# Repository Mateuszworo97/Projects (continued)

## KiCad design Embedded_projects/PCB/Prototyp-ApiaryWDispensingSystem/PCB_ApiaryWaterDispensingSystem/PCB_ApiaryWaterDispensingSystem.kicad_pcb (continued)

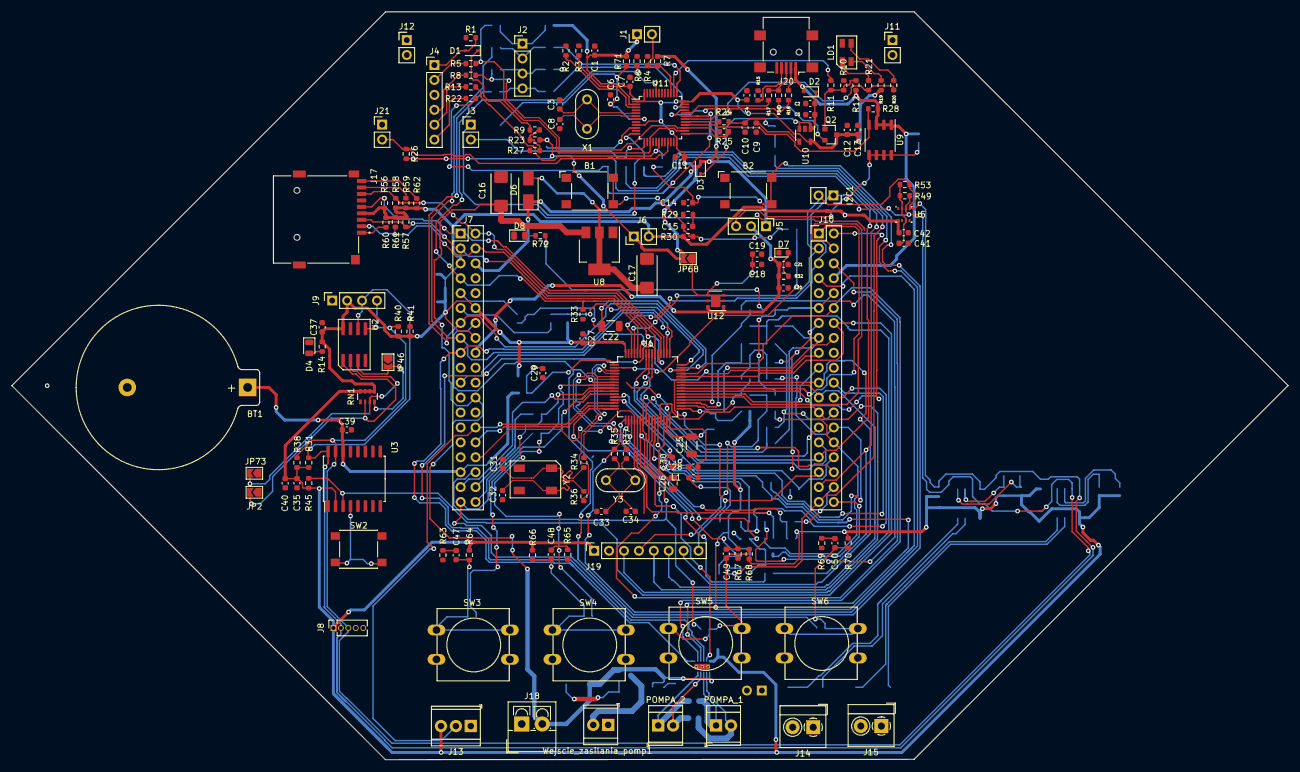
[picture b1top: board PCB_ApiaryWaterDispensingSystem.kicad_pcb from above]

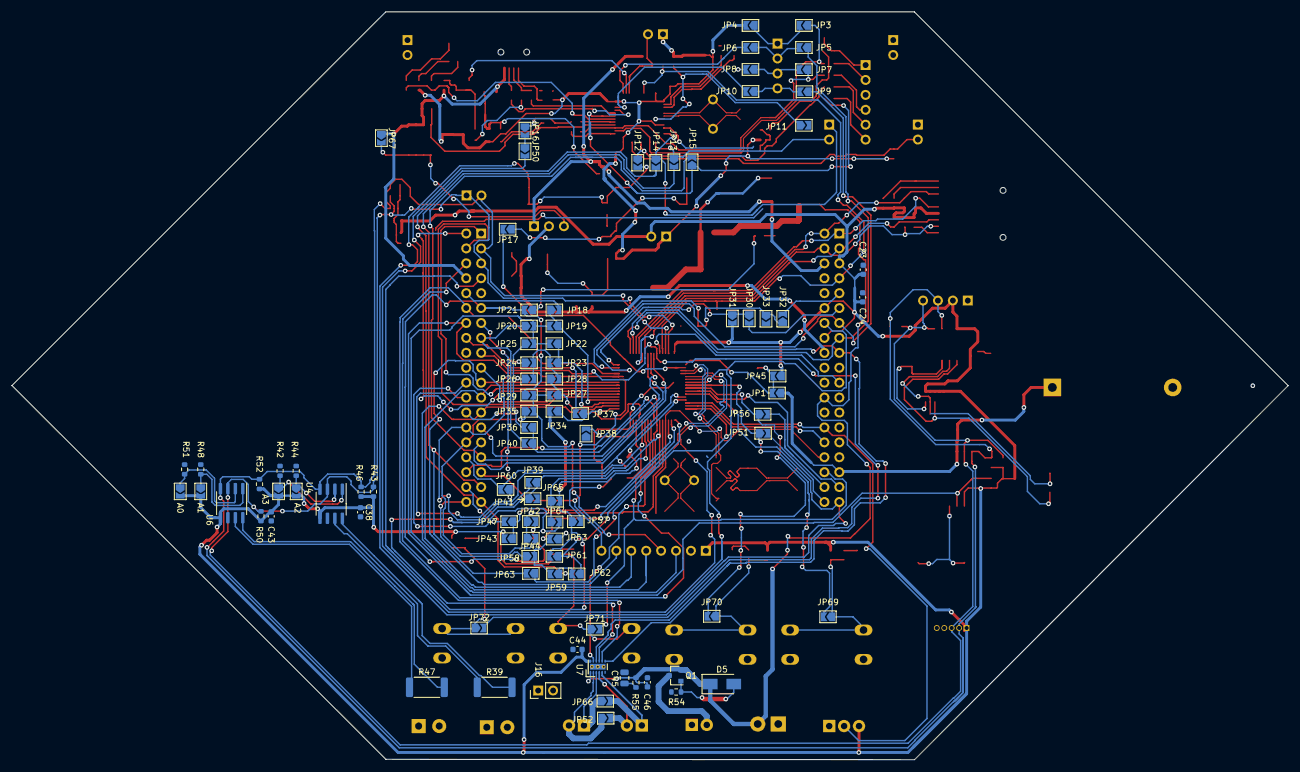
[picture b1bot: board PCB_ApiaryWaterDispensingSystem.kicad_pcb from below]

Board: 2 copper layers, 217.3 x 127.3 mm, 255 parts (94 on the bottom side), 180 nets.

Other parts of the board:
C44, C46: 100n; C_0603_1608Metric
C45: 10u; C_0805_2012Metric
D5: D_Schottky 6,8 V SMAZ6V8; D_SMA
D6: D_Small; D_SMA
D7: LED; D_0603_1608Metric
J16, J21: Conn_02x01; PinHeader_1x02_P2.54mm_Vertical
J18: Conn_01x02; TerminalBlock_4Ucon_1x02_P3.50mm_Vertical
J20: USB_B_Micro; USB_Mini-B_Lumberg_2486_01_Horizontal
JP52, JP66: Jumper_NO_Small; SolderJumper-2_P1.3mm_Open_TrianglePad1.0x1.5mm
JP67, JP68: Jumper_2_Open; SolderJumper-2_P1.3mm_Open_TrianglePad1.0x1.5mm
LD1: LD_BICOLOR_CMS; LD_BiCOLOR_CMS
Q1: Q_PMOS_GSD; SOT-23
Q2: Q_NPN_BEC; SOT-23
R54, R71: 100k; R_0603_1608Metric
R55: 1; R_0603_1608Metric
U7: drv8835; WSON-12-1EP_3x2mm_P0.5mm_EP1x2.65_ThermalVias
U8: LD1117S50TR_SOT223; SOT-223-3_TabPin2
U9: STS7PF30L; SO-8_3.9x4.9mm_P1.27mm
U10: LD3985M33R_SOT23; SOT-23-5
U11: STM32F103CBTx; LQFP-48_7x7mm_P0.5mm
U12: LD39050PU33; WSON-6-1EP_3x3mm_P0.95mm
Wejscie_zasilania_pomp1: Conn_01x02; TerminalBlock_TE_282834-2_1x02_P2.54mm_Horizontal

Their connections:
+5V: U12.1, U12.6; also elsewhere on the board
+5VA: D6.1; also elsewhere on the board
+5VP: J20.1, JP67.1, U9.1, U9.2, U9.3; also elsewhere on the board
/Microcontroller_F1/OSC+: U11.5; also elsewhere on the board
/Microcontroller_F1/OSC-: U11.6; also elsewhere on the board
AENABLE: U7.9; also elsewhere on the board
AIN_1: U11.10; also elsewhere on the board
APHASE: U7.10; also elsewhere on the board
BENABLE: U7.7; also elsewhere on the board
BOOT0: U11.44; also elsewhere on the board
BPHASE: U7.8; also elsewhere on the board
GNDA: C45.2, C46.2, J16.2, R54.2, Wejscie_zasilania_pomp1.1
LED_STLINK: U11.30; also elsewhere on the board
MODE: U7.11; also elsewhere on the board
unnamed 48: U10.1, U10.3; also elsewhere on the board
unnamed 49: U10.4; also elsewhere on the board
unnamed 52: D6.2, U8.2; also elsewhere on the board
unnamed 53: JP68.1, U12.4; also elsewhere on the board
unnamed: C45.1, R55.2
unnamed: D5.2, Q1.1, R54.1
unnamed 70: D7.2; also elsewhere on the board
unnamed 79: JP67.2, U9.5, U9.6, U9.7, U9.8; also elsewhere on the board
unnamed 86: J20.2; also elsewhere on the board
unnamed 87: J20.3; also elsewhere on the board
unnamed 88: J20.4; also elsewhere on the board
unnamed 105: LD1.2; also elsewhere on the board
unnamed 106: LD1.3; also elsewhere on the board
unnamed 107: LD1.4; also elsewhere on the board
unnamed 108: Q2.1; also elsewhere on the board
unnamed 109: Q2.2; also elsewhere on the board
unnamed 110: U11.3; also elsewhere on the board
unnamed 111: U11.2; also elsewhere on the board
unnamed 112: U11.29; also elsewhere on the board
PWR_ENn: U9.4, U11.28; also elsewhere on the board
PWR_EXT: U11.39; also elsewhere on the board
STM_JTCK: U11.37; also elsewhere on the board
STM_JTMS: U11.34; also elsewhere on the board
STM_RST: R71.1, U11.7; also elsewhere on the board
ST_LINK_RX: U11.13; also elsewhere on the board
ST_LINK_TX: U11.12; also elsewhere on the board
T_JTCK: U11.15, U11.26; also elsewhere on the board
T_JTMS: U11.27; also elsewhere on the board
T_NRST: U11.18; also elsewhere on the board
T_SWDIO_IN: U11.25; also elsewhere on the board
T_SWO: U11.31; also elsewhere on the board
USB_DM: U11.32; also elsewhere on the board
USB_DP: U11.33; also elsewhere on the board
USB_RENUMn: U11.38; also elsewhere on the board
VDD: C44.1, U7.12; also elsewhere on the board
VIN: Q1.3, Wejscie_zasilania_pomp1.2
VM: C46.1, D5.1, J18.2, Q1.2, R55.1, U7.1, U8.3; also elsewhere on the board

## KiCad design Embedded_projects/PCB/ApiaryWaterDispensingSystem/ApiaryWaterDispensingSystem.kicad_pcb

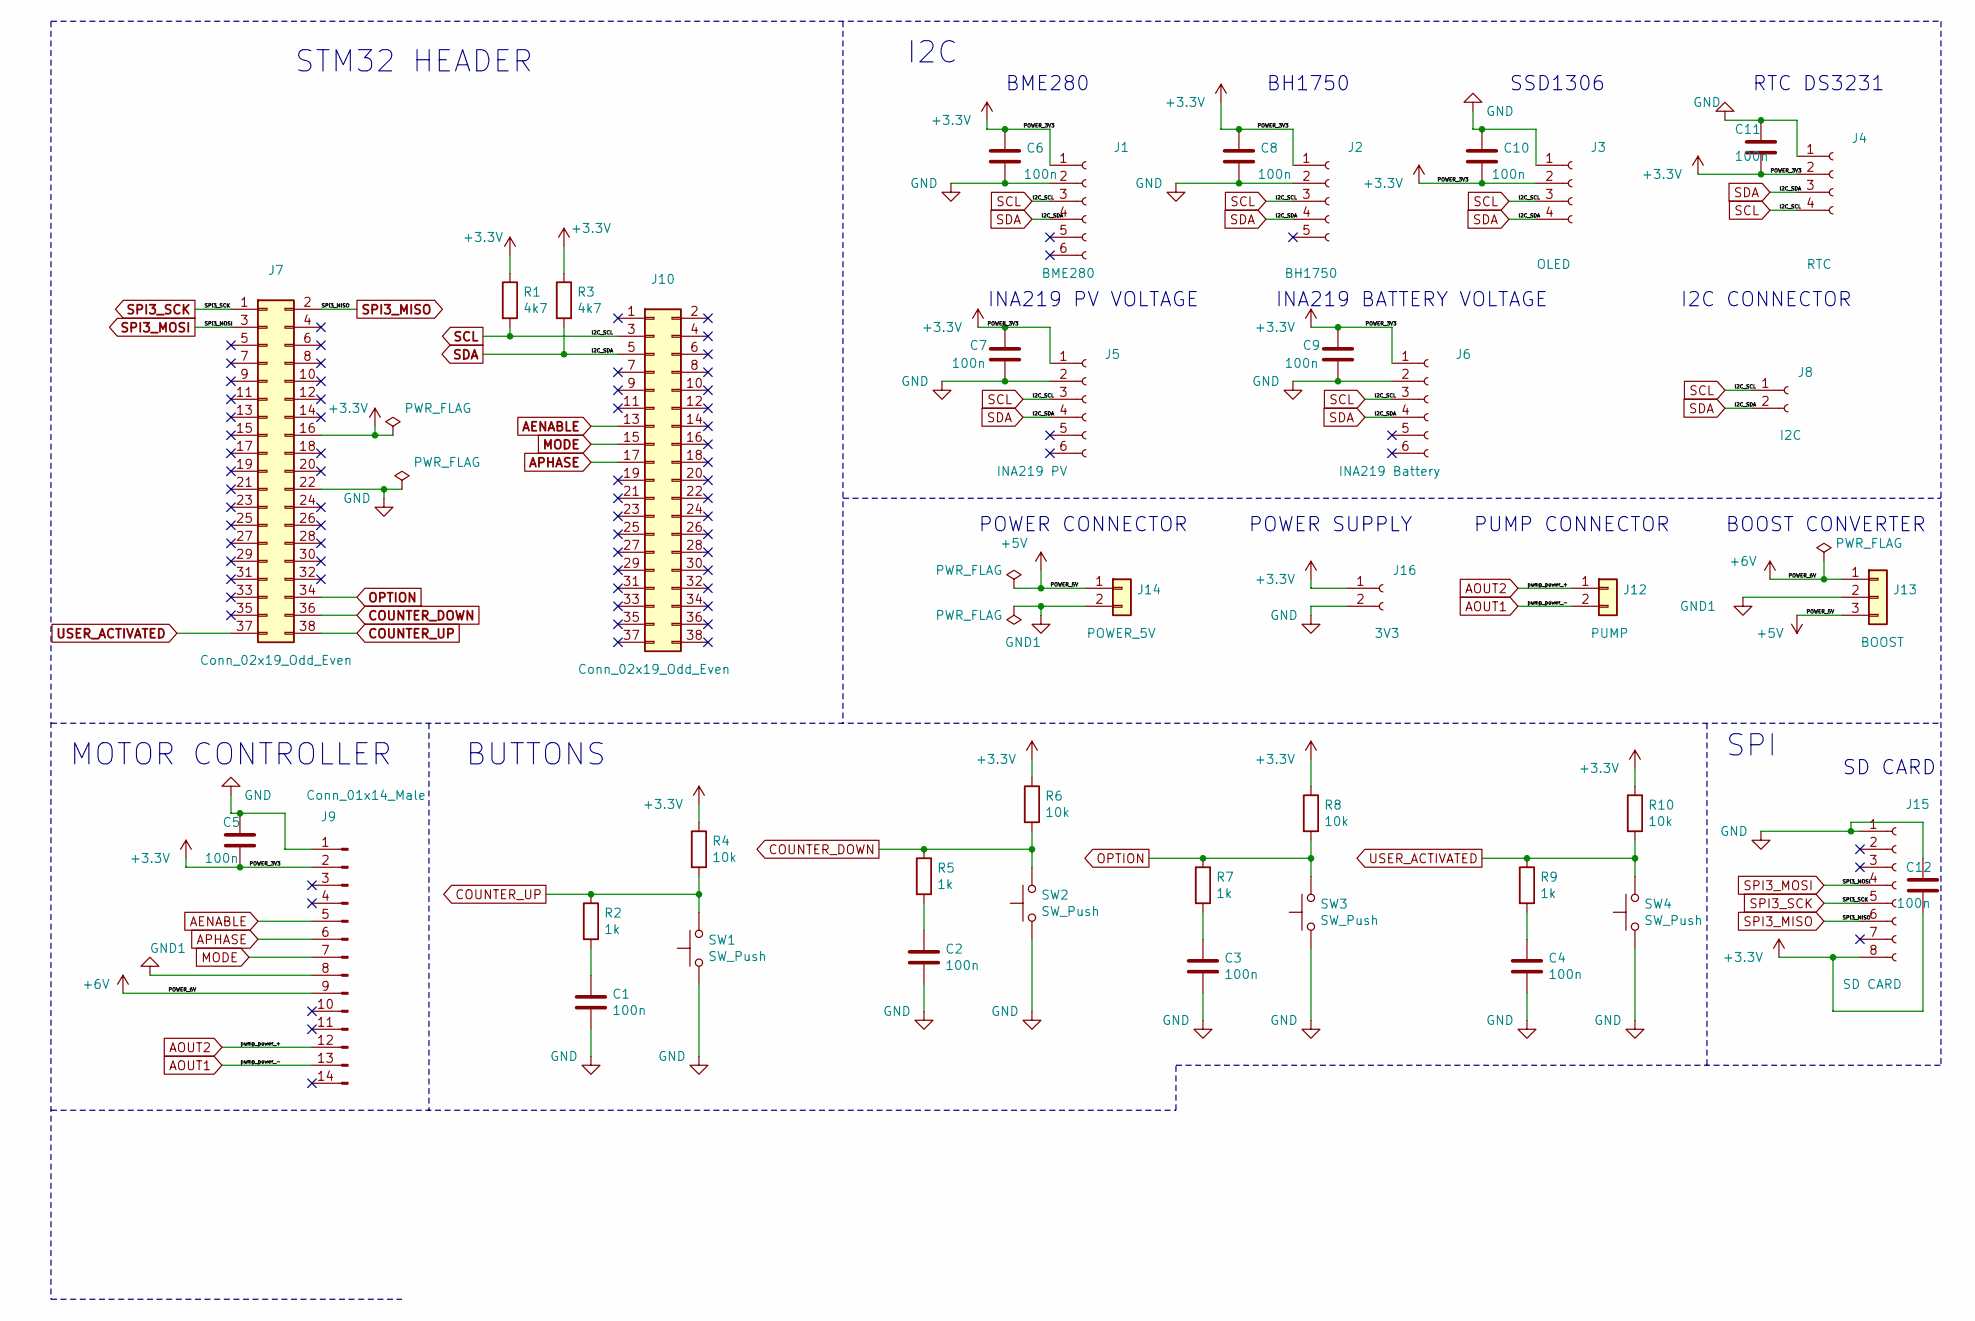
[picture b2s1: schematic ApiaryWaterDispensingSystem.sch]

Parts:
C1, C2, C3, C4, C5, C6, C7, C8, C9, C10, C11, C12: 100n; C_0805_2012Metric
J1: BME280; PinSocket_1x06_P2.54mm_Vertical_BME280
J2: BH1750; PinSocket_1x05_P2.54mm_Vertical
J3: OLED; PinSocket_1x04_P2.54mm_Vertical
J4: RTC; PinSocket_1x04_P2.54mm_Vertical_RTCDS3231
J5: INA219 PV; PinSocket_1x06_P2.54mm_Vertical
J6: INA219 Battery; PinSocket_1x06_P2.54mm_Vertical
J7, J10: Conn_02x19_Odd_Even; PinSocket_2x19_P2.54mm_Vertical
J8: I2C; PinSocket_1x02_P2.54mm_Vertical
J9: Conn_01x14_Male; PinSocket_1x07_P2.54mm_Vertical_DRV8835
J12: PUMP; TerminalBlock_TE_282834-2_1x02_P2.54mm_Horizontal
J13: BOOST; PinSocket_1x03_P2.00mm_Vertical
J14: POWER_5V; TerminalBlock_TE_282834-2_1x02_P2.54mm_Horizontal
J15: SD CARD; PinSocket_1x08_P2.54mm_Vertical_SD_CARD
J16: 3V3; PinSocket_1x02_P2.54mm_Vertical
R1, R3: 4k7; R_0805_2012Metric
R2, R5, R7, R9: 1k; R_0805_2012Metric
R4, R6, R8, R10: 10k; R_0805_2012Metric
SW1, SW2, SW3, SW4: SW_Push; SW_PUSH-12mm

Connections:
+3V3: C5.2, C6.1, C7.1, C8.1, C9.1, C10.2, C11.2, C12.2, J1.1, J2.1, J3.2, J4.2, J5.1, J6.1, J7.16, J9.2, J15.8, J16.1, R1.1, R3.1, R4.1, R6.1, R8.1, R10.1
+5V: J13.3, J14.1
+6V: J9.9, J13.1
AENABLE: J9.5, J10.13
AOUT1: J9.13, J12.2
AOUT2: J9.12, J12.1
APHASE: J9.6, J10.17
COUNTER_DOWN: J7.36, R5.1, R6.2, SW2.2
COUNTER_UP: J7.38, R2.1, R4.2, SW1.2
GND: C1.2, C2.2, C3.2, C4.2, C5.1, C6.2, C7.2, C8.2, C9.2, C10.1, C11.1, C12.1, J1.2, J2.2, J3.1, J4.1, J5.2, J6.2, J7.22, J9.1, J15.1, J16.2, SW1.1, SW2.1, SW3.1, SW4.1
GND1: J9.8, J13.2, J14.2
MODE: J9.7, J10.15
unnamed: C1.1, R2.2
unnamed: C2.1, R5.2
unnamed: C3.1, R7.2
unnamed: C4.1, R9.2
OPTION: J7.34, R7.1, R8.2, SW3.2
SCL: J1.3, J2.3, J3.3, J4.4, J5.3, J6.3, J8.1, J10.3, R1.2
SDA: J1.4, J2.4, J3.4, J4.3, J5.4, J6.4, J8.2, J10.5, R3.2
SPI3_MISO: J7.2, J15.6
SPI3_MOSI: J7.3, J15.4
SPI3_SCK: J7.1, J15.5
USER_ACTIVATED: J7.37, R9.1, R10.2, SW4.2

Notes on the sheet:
STM32 HEADER
I2C
BH1750
SSD1306
INA219 PV VOLTAGE
INA219 BATTERY VOLTAGE
SD CARD
RTC DS3231
BME280
PUMP CONNECTOR
I2C CONNECTOR
BOOST CONVERTER
SPI
POWER SUPPLY
BUTTONS
POWER CONNECTOR
MOTOR CONTROLLER

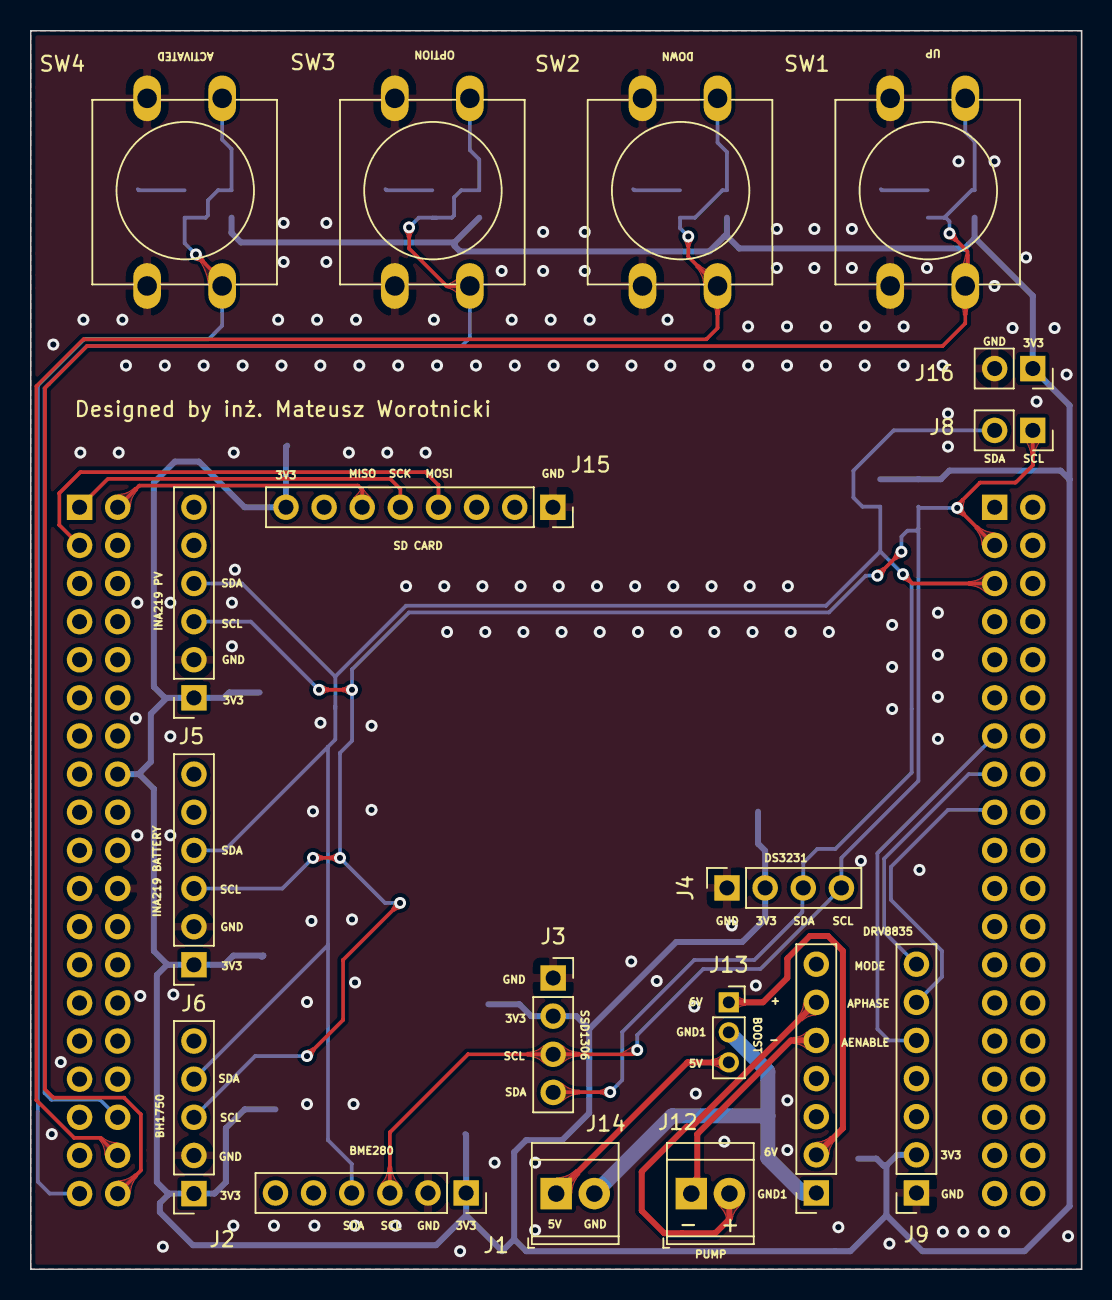
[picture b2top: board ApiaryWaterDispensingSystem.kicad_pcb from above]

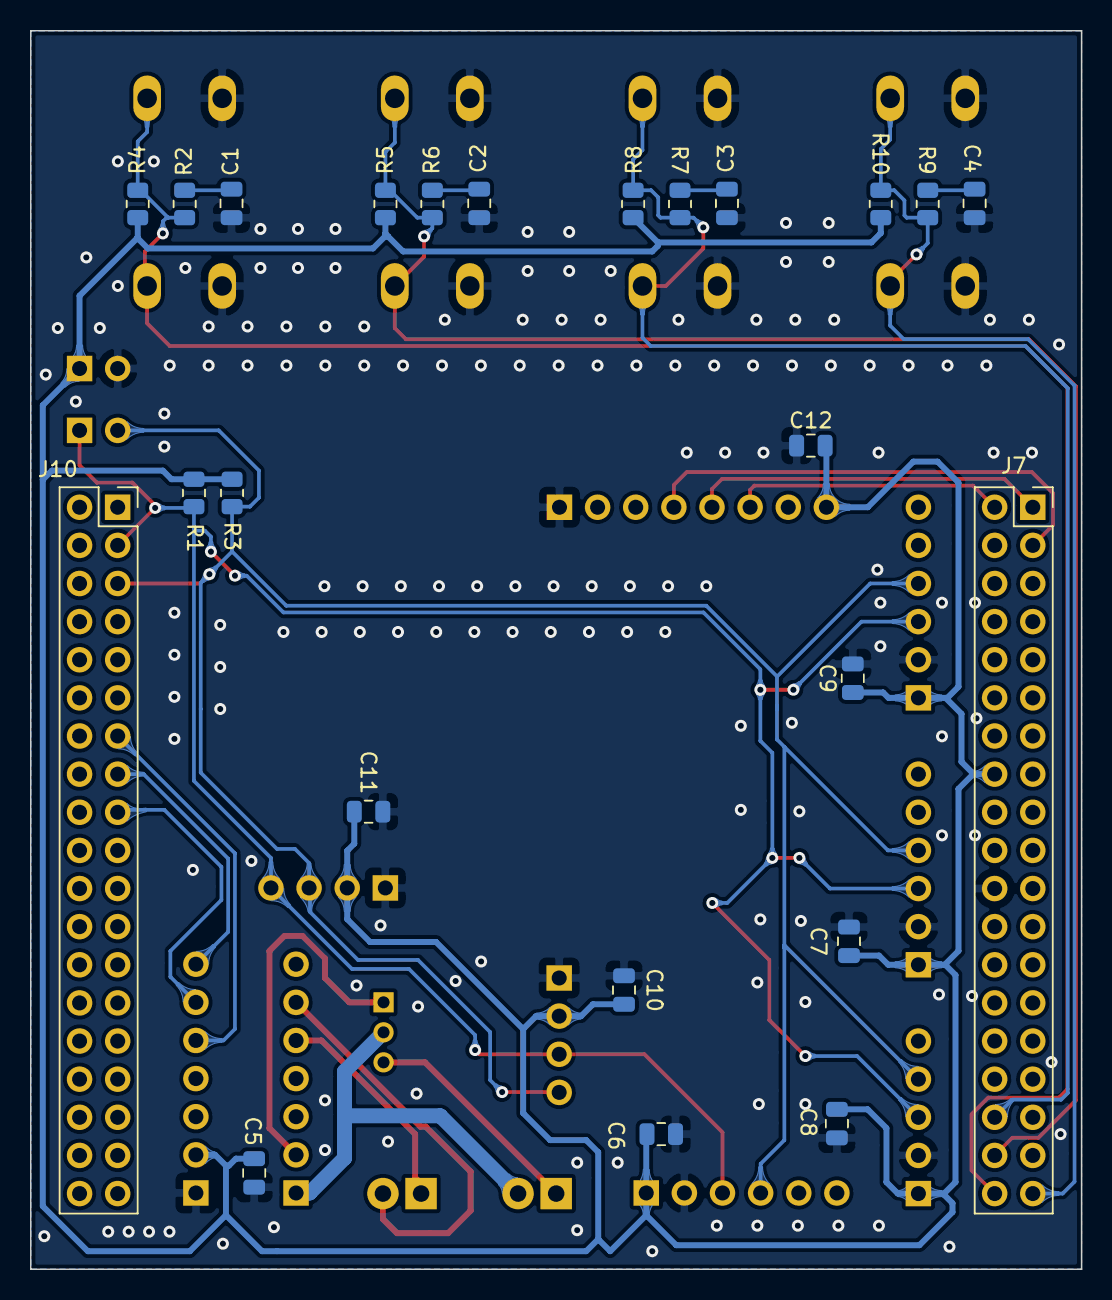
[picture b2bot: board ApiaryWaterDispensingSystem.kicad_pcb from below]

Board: 2 copper layers, 70.0 x 82.5 mm, 41 parts (24 on the bottom side), 23 nets.

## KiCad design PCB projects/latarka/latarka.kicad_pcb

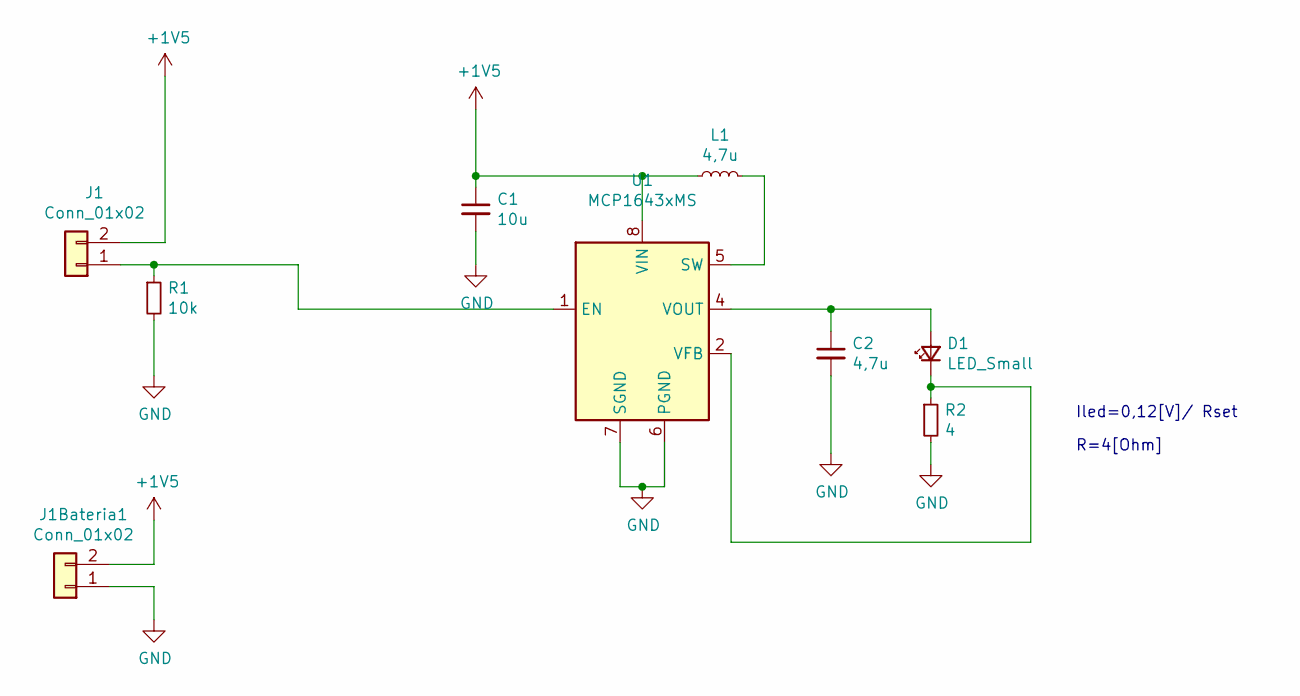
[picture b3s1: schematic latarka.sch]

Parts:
C1: 10u; C_0805_2012Metric_Pad1.18x1.45mm_HandSolder
C2: 4,7u; C_0805_2012Metric_Pad1.18x1.45mm_HandSolder
D1: LED_Small; LED_D8.0mm
J1, J1Bateria1: Conn_01x02; PinHeader_1x02_P2.54mm_Vertical
L1: 4,7u; cewka_m2
R1: 10k; R_0805_2012Metric_Pad1.20x1.40mm_HandSolder
R2: 4; R_0805_2012Metric_Pad1.20x1.40mm_HandSolder
U1: MCP1643xMS; MSOP-8_3x3mm_P0.65mm

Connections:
+1V5: C1.1, J1.2, J1Bateria1.2, L1.1, U1.8 (VIN)
GND: C1.2, C2.2, J1Bateria1.1, R1.2, R2.2, U1.6 (PGND), U1.7 (SGND)
unnamed: C2.1, D1.2 (A), U1.4 (VOUT)
unnamed: D1.1 (K), R2.1, U1.2 (VFB)
unnamed: J1.1, R1.1, U1.1 (EN)
unnamed: L1.2, U1.5 (SW)

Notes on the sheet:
Iled=0,12[V]/ Rset
R=4[Ohm]

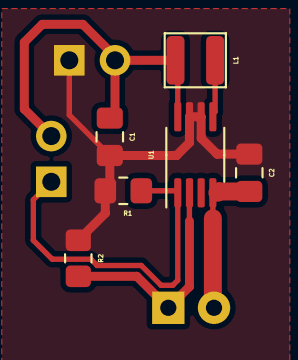
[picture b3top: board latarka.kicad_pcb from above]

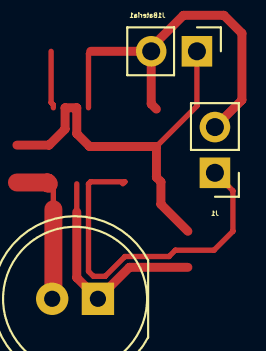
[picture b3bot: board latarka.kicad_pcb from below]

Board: 2 copper layers, 9 parts (3 on the bottom side), 6 nets.

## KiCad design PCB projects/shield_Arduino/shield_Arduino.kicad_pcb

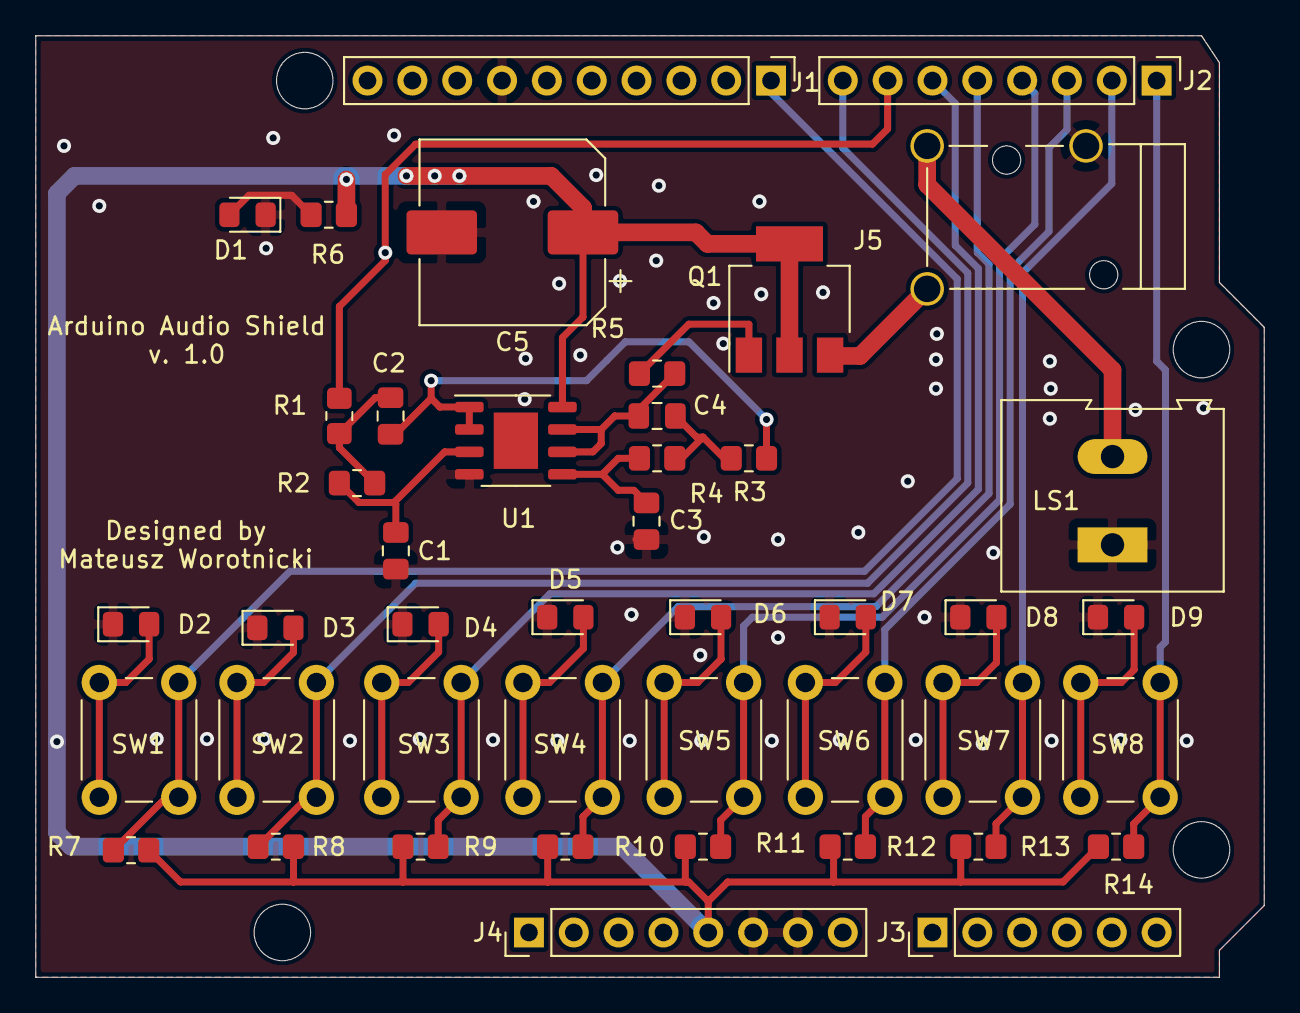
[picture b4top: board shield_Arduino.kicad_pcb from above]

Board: 2 copper layers, 69.6 x 53.3 mm, 45 parts (0 on the bottom side), 29 nets.

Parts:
C1, C3: 1nF; C_0805_2012Metric_Pad1.18x1.45mm_HandSolder
C2: 27n; C_0805_2012Metric_Pad1.18x1.45mm_HandSolder
C4: 56mF; C_0805_2012Metric_Pad1.18x1.45mm_HandSolder
C5: 1000uF; CP_Elec_10x10
D1, D2, D3, D4, D5, D6, D7, D8, D9: LED; LED_0805_2012Metric_Pad1.15x1.40mm_HandSolder
J1: Conn_01x10_Male; PinHeader_1x10_P2.54mm_Vertical
J2, J4: Conn_01x08_Male; PinHeader_1x08_P2.54mm_Vertical
J3: Conn_01x06_Male; PinHeader_1x06_P2.54mm_Vertical
J5: AudioJack2_SwitchT; Jack_3.5mm_Lumberg_150304_Horizontal
LS1: Speaker; TerminalBlock_Altech_AK300-2_P5.00mm
Q1: BCP56; SOT-223-3_TabPin2
R1: 13k; R_0805_2012Metric_Pad1.20x1.40mm_HandSolder
R2: 27k; R_0805_2012Metric_Pad1.20x1.40mm_HandSolder
R3: 1k6; R_0805_2012Metric_Pad1.20x1.40mm_HandSolder
R4: 3k; R_0805_2012Metric_Pad1.20x1.40mm_HandSolder
R5: 120; R_0805_2012Metric_Pad1.20x1.40mm_HandSolder
R6, R7, R8, R9, R10, R11, R12, R13, R14: 220; R_0805_2012Metric_Pad1.20x1.40mm_HandSolder
SW1, SW2, SW3, SW4, SW5, SW6, SW7, SW8: SWITCH; SW_PUSH_6mm_H5mm
U1: MCP6002-xSN; SOIC-8-1EP_3.9x4.9mm_P1.27mm_EP2.514x3.2mm
e: MountingHole_3.2mm_M3

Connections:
+5V: C5.1, J4.5, Q1.2, R6.1, R7.1, R8.1, R9.1, R10.1, R11.1, R12.1, R13.1, R14.1, U1.8
/AUDIO_WAVE: C4.1, R5.2, U1.6, U1.7
AUDIO_PWM: J2.7, R1.2
BTN_1: J2.1, R14.2, SW8.2
BTN_2: J2.2, R13.2, SW7.2
BTN_3: J2.3, R12.2, SW6.2
BTN_4: J2.4, R11.2, SW5.2
BTN_5: J2.5, R10.2, SW4.2
BTN_6: J2.6, R9.2, SW3.2
BTN_7: J2.8, R8.2, SW2.2
BTN_8: J1.1, R7.2, SW1.2
GND: C1.2, C3.2, C5.2, D1.1, D2.1, D3.1, D4.1, D5.1, D6.1, D7.1, D8.1, D9.1, J1.7, J4.6, J4.7, J5.S, LS1.1, U1.4
unnamed: C1.1, R2.1, U1.3
unnamed: C2.1, R3.2, U1.1, U1.2
unnamed: C2.2, R1.1, R2.2
unnamed: C3.1, R4.1, U1.5
unnamed: C4.2, R3.1, R4.2
unnamed: D1.2, R6.2
unnamed: D2.2, SW1.1
unnamed: D3.2, SW2.1
unnamed: D4.2, SW3.1
unnamed: D5.2, SW4.1
unnamed: D6.2, SW5.1
unnamed: D7.2, SW6.1
unnamed: D8.2, SW7.1
unnamed: D9.2, SW8.1
unnamed: J5.T, Q1.3
unnamed: J5.TN, LS1.2
unnamed: Q1.1, R5.1

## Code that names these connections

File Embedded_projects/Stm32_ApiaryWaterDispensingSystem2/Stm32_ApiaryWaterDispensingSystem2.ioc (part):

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Mcu.Name=STM32F411R(C-E)Tx
Mcu.Package=LQFP64
Mcu.UserName=STM32F411RETx
PA0-WKUP.Signal=ADCx_IN0
PA10.GPIOParameters=GPIO_Label
PA10.GPIO_Label=BACKLIGHT
PA10.Signal=GPIO_Output
PA11.GPIOParameters=GPIO_Label
PA11.GPIO_Label=SQW
PA11.Signal=GPIO_Input
PA12.GPIOParameters=GPIO_Label
PA12.GPIO_Label=BPHASE
PA12.Signal=GPIO_Output
PA13.GPIOParameters=GPIO_Label
PA13.GPIO_Label=TMS
PA13.Mode=Serial_Wire
PA13.Signal=SYS_JTMS-SWDIO
PA14.GPIOParameters=GPIO_Label
PA14.GPIO_Label=TCK
PA14.Mode=Serial_Wire
PA14.Signal=SYS_JTCK-SWCLK
PA15.GPIOParameters=GPIO_Label
PA15.GPIO_Label=BENABLE
PA15.Signal=S_TIM2_CH1_ETR
PA2.GPIOParameters=GPIO_Label
PA2.GPIO_Label=USART_TX
PA2.Mode=Asynchronous
PA2.Signal=USART2_TX
PA3.GPIOParameters=GPIO_Label
PA3.GPIO_Label=USART_RX
PA3.Mode=Asynchronous
PA3.Signal=USART2_RX
PA5.GPIOParameters=GPIO_Label
PA5.GPIO_Label=LD2 [Green Led]
PA5.Signal=GPIO_Output
PA6.GPIOParameters=GPIO_Label
PA6.GPIO_Label=AENABLE
PA6.Signal=S_TIM3_CH1
PA7.GPIOParameters=GPIO_Label
PA7.GPIO_Label=MODE
PA7.Signal=GPIO_Output
PA8.GPIOParameters=GPIO_Label
PA8.GPIO_Label=DC_DISPLAY
PA8.Signal=GPIO_Output
PA9.GPIOParameters=GPIO_Label
PA9.GPIO_Label=RST_DISPLAY
PA9.Signal=GPIO_Output
PB0.GPIOParameters=GPIO_PuPd,GPIO_Label
PB0.GPIO_Label=B3
PB0.GPIO_PuPd=GPIO_PULLUP
PB0.Signal=GPIO_Input
PB10.GPIOParameters=GPIO_Speed,PinState,GPIO_PuPd,GPIO_Label
PB10.GPIO_Label=SPI2_CS
PB10.GPIO_PuPd=GPIO_NOPULL
PB10.GPIO_Speed=GPIO_SPEED_FREQ_LOW
PB10.PinState=GPIO_PIN_RESET
PB10.Signal=GPIO_Output
PB13.Mode=Full_Duplex_Master
PB13.Signal=SPI2_SCK
PB15.Mode=Full_Duplex_Master
PB15.Signal=SPI2_MOSI
PB3.GPIOParameters=GPIO_Label
PB3.GPIO_Label=SWO
PB3.Signal=SYS_JTDO-SWO
PB6.GPIOParameters=GPIO_Label
PB6.GPIO_Label=APHASE
PB6.Signal=GPIO_Output
PB8.Mode=I2C
PB8.Signal=I2C1_SCL
PB9.Mode=I2C
PB9.Signal=I2C1_SDA
PC0.GPIOParameters=GPIO_PuPd,GPIO_Label
PC0.GPIO_Label=B1
PC0.GPIO_PuPd=GPIO_PULLUP
PC0.Signal=GPIO_Input
PC1.GPIOParameters=GPIO_PuPd,GPIO_Label
PC1.GPIO_Label=B2
PC1.GPIO_PuPd=GPIO_PULLUP
PC1.Signal=GPIO_Input
PC10.GPIOParameters=GPIO_PuPd
PC10.GPIO_PuPd=GPIO_NOPULL
PC10.Mode=Full_Duplex_Master
PC10.Signal=SPI3_SCK
PC11.GPIOParameters=GPIO_PuPd
PC11.GPIO_PuPd=GPIO_NOPULL
PC11.Mode=Full_Duplex_Master
PC11.Signal=SPI3_MISO
PC12.GPIOParameters=GPIO_PuPd
PC12.GPIO_PuPd=GPIO_NOPULL
PC12.Mode=Full_Duplex_Master
PC12.Signal=SPI3_MOSI
PC14-OSC32_IN.Mode=LSE-External-Oscillator
PC14-OSC32_IN.Signal=RCC_OSC32_IN
PC15-OSC32_OUT.Mode=LSE-External-Oscillator
PC15-OSC32_OUT.Signal=RCC_OSC32_OUT
PC2.Mode=Full_Duplex_Master
PC2.Signal=SPI2_MISO
PC3.GPIOParameters=GPIO_PuPd,GPIO_Label
PC3.GPIO_Label=B4
PC3.GPIO_PuPd=GPIO_PULLUP
PC3.Signal=GPIO_Input
PD2.GPIOParameters=GPIO_Label
PD2.GPIO_Label=SPI3_CS
PD2.Signal=GPIO_Output
PH0\ -\ OSC_IN.Mode=HSE-External-Clock-Source
PH0\ -\ OSC_IN.Signal=RCC_OSC_IN
PH1\ -\ OSC_OUT.Mode=HSE-External-Clock-Source
PH1\ -\ OSC_OUT.Signal=RCC_OSC_OUT
RCC.HSE_VALUE=8000000
RCC.SYSCLKFreq_VALUE=84000000
RCC.SYSCLKSource=RCC_SYSCLKSOURCE_PLLCLK
board=NUCLEO-F411RE
boardIOC=true

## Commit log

2024-02-26 Create PCB projects
2024-02-26 -added KiCad project
2024-02-26 adding a flashlight design
    -Thanks to the integrated circuit, the system is able to operate at a lower battery cell voltage.
2024-02-29 + project configuration
    +added bh1750, bme280,ssd1306
    +configuration RTC
    +led blinking
2024-02-29 +SSD1306 task
    checking i2c communication
2024-02-29 - data display
    calculation and display of parameters on the display in real time
2024-03-02 adding and displaying the time on the display SSD1306
2024-03-03 Rename README.md to README.rst
2024-03-03 +added Alarm 1 to the RTC
2024-03-08 Create docs
2024-03-15 +update hardware.drawio
    +added drv_8835 library
    + update diagram hardware
2024-03-19 +bugs fix
2024-03-20 +bugs fixes
    +added project, which is connecting with stm32f411re
2024-03-20 + activate the alarm correctness
    possibility of changing the pump activation for a specified number of minutes from 1 to 59
    - cyclical settings for turning on the pump after the alarm is triggered from 8 a.m. to 10 p.m
2024-03-20 update software.drawio
    +adding graphs
2024-04-07 +update projects
2024-06-25 Update Kicad
    +update eeschema
2024-07-11 +update project
    positive test
2024-11-10 main: Ucgosu
2024-11-18 updated file README.rst
2024-11-18 updated file README.rst
2024-11-18 adding design photos
2025-01-28 commit : master
2025-01-28 resolve conflicts
2025-01-28 resolves problems
2025-01-28 changes projects
2025-01-28 _fixed bugs
2025-01-28 repair -bugs
2025-01-28 -added repair files
2025-01-28 created user_control files
2025-01-28 changes user_control
2025-02-04 added machine states in file : button.c and button.h #7
2025-02-22 modfied button.h button.c freertos.c and main.c -> change of control user
2025-02-26 #7 Improved code readability, addding a state machine : idle, debounce, pressed, repeat. Expanding functionality with system interactions with user
2025-03-07 increasing code readability: #7
2025-03-07 development of second protoype #3
2025-03-14 added file ds3231.sch #3
2025-03-20 added BME280 sensor to the project , #3
2025-03-20 added ina219 to the project #3
2025-03-29 added x-tal and his footprints for microcontroller schematics, user button
2025-03-30 stm32f411re completed schematic
2025-03-31 added elements of stm32F103CBT6
2025-04-01 F1 completed
2025-04-03 added changes of Microntroller_F4 ->global variables #3
2025-06-24 added lot of changes to project #3
2025-10-15 Many design changes have been added over the past few months #3
2025-11-04 All signal has been routed, the analog part needs to be completed
2025-11-04 The file has been updated and added visualization.png
2025-11-04 added visualization.png
2025-11-04 added the correct version
2025-11-04 added html in readme.RST
2025-11-14 update html in readme.RST and improved PCb #3
2025-11-14 update html in readme.RST #3
